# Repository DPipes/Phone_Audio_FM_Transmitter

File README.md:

# Phone Audio FM Transmitter

A device that connects to a smartphone over Bluetooth and transmits the phone's audio over FM. This allows users to listen to their phones over the radio of cars that do not otherwise offer that functionality. In contrast to similar devices on the market, this can scan the FM band and identify an open channel to broadcast on so the user only has to set their car radio to the same station.

This is an electrical engineering senior design project for ECE 445 at the University of Illinois - Urbana Champaign

Team Members:
 - James W.
 - Madigan C.
 - Dan P.

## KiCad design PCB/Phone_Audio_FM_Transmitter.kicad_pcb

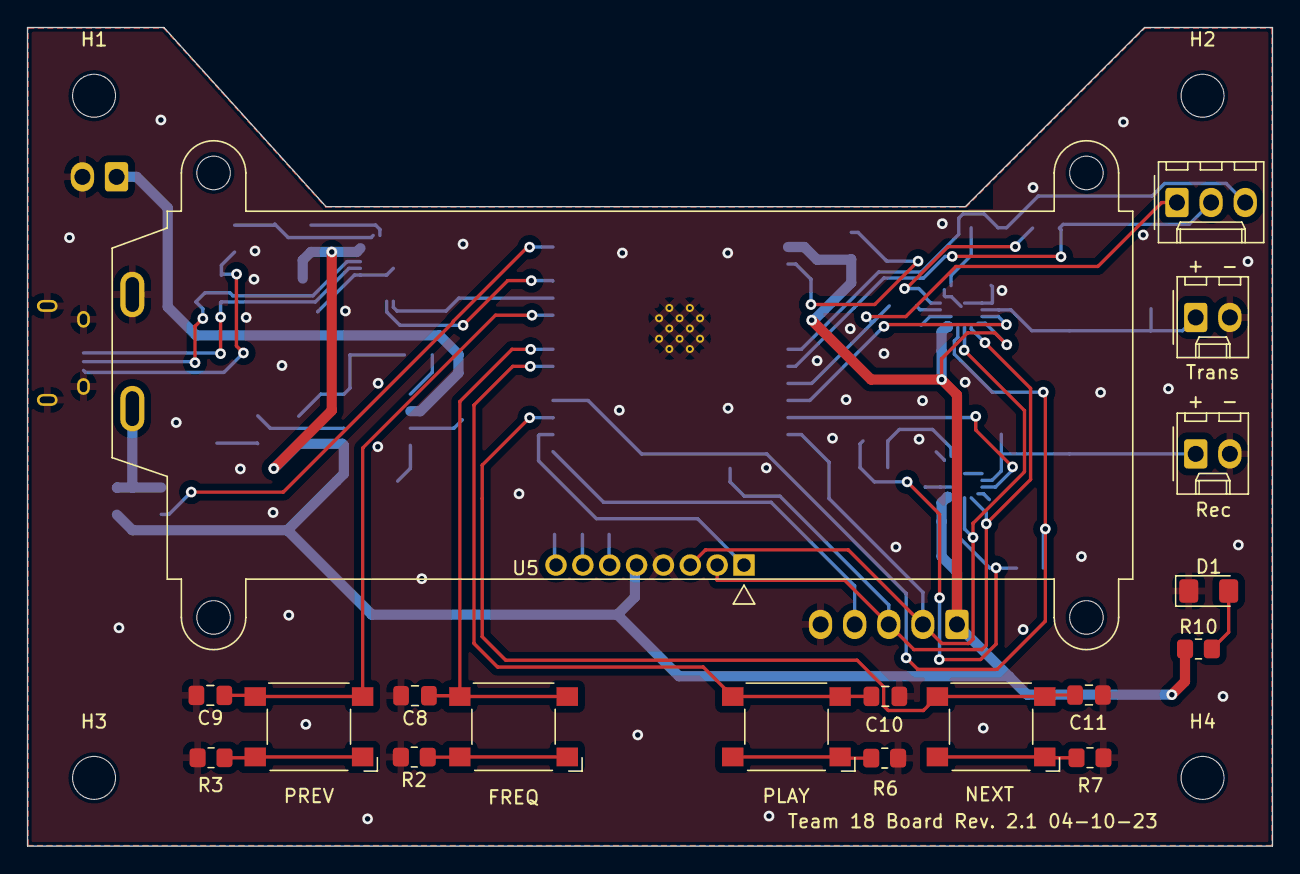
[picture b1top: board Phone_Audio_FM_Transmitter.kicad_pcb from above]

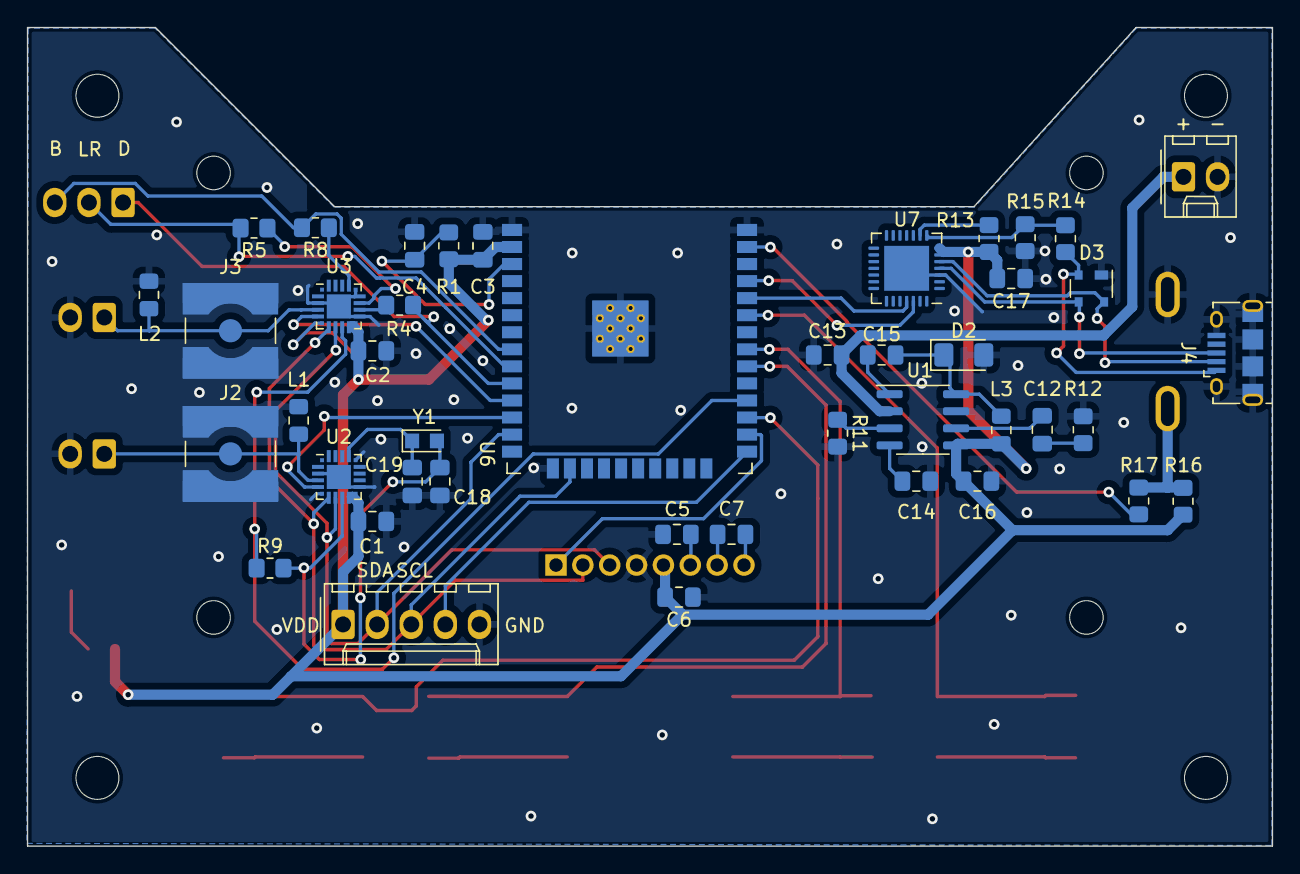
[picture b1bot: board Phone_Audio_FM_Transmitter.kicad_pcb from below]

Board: 2 copper layers, 92.7 x 61.0 mm, 65 parts (43 on the bottom side), 48 nets.

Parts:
C1, C2, C3, C6, C17: 10uF; C_0805_2012Metric_Pad1.18x1.45mm_HandSolder
C4, C5, C7, C8, C9, C10, C11: 1uF; C_0805_2012Metric_Pad1.18x1.45mm_HandSolder
C12: 0.22uF; C_0805_2012Metric_Pad1.18x1.45mm_HandSolder
C13, C16: 22uF; C_0805_2012Metric_Pad1.18x1.45mm_HandSolder
C14: 12nF; C_0805_2012Metric_Pad1.18x1.45mm_HandSolder
C15: 0.1uF; C_0805_2012Metric_Pad1.18x1.45mm_HandSolder
C18, C19: 22pF; C_0805_2012Metric_Pad1.18x1.45mm_HandSolder
D1: LED; LED_1206_3216Metric_Pad1.42x1.75mm_HandSolder
D2: D_Schottky; D_1206_3216Metric_Pad1.42x1.75mm_HandSolder
D3: SP0503BAHT; SOT-143
H1, H2, H3, H4: MountingHole; MountingHole_3.2mm_M3
J1: Vin; Molex_KK-254_AE-6410-02A_1x02_P2.54mm_Vertical
J2, J3: Conn_Coaxial; SMA_Amphenol_132134-10_Vertical
J4: USB_B_Micro; USB_Micro-B_Amphenol_10118194_Horizontal
J5: Test Point; Molex_KK-254_AE-6410-05A_1x05_P2.54mm_Vertical
J6: Rec; Molex_KK-254_AE-6410-02A_1x02_P2.54mm_Vertical
J7: Trans; Molex_KK-254_AE-6410-02A_1x02_P2.54mm_Vertical
J8: I2S Test Point; Molex_KK-254_AE-6410-03A_1x03_P2.54mm_Vertical
L1, L2: 120nH; L_0805_2012Metric_Pad1.15x1.40mm_HandSolder
L3: 13uH; L_0805_2012Metric_Pad1.15x1.40mm_HandSolder
R1, R2, R3, R6, R7, R10: 10k; R_0805_2012Metric_Pad1.20x1.40mm_HandSolder
R4: 600; R_0805_2012Metric_Pad1.20x1.40mm_HandSolder
R5, R8: 2k; R_0805_2012Metric_Pad1.20x1.40mm_HandSolder
R9: 0; R_0805_2012Metric_Pad1.20x1.40mm_HandSolder
R11: 82k; R_0805_2012Metric_Pad1.20x1.40mm_HandSolder
R12: 2.2k; R_0805_2012Metric_Pad1.20x1.40mm_HandSolder
R13: 1k; R_0805_2012Metric_Pad1.20x1.40mm_HandSolder
R14: 22.1k; R_0805_2012Metric_Pad1.20x1.40mm_HandSolder
R15: 47.5k; R_0805_2012Metric_Pad1.20x1.40mm_HandSolder
R16, R17: 100; R_0805_2012Metric_Pad1.20x1.40mm_HandSolder
SW1, SW2, SW3, SW4: SW_Push; SW_SPST_Omron_B3FS-101xP
U1: TPS5403; SOIC-8_3.9x4.9mm_P1.27mm
U2: Si4706; SiliconLabs_QFN-20-1EP_3x3mm_P0.5mm_EP1.8x1.8mm
U3: Si4711; SiliconLabs_QFN-20-1EP_3x3mm_P0.5mm_EP1.8x1.8mm
U5: NHD-C0220BIZ; NHD-C0220BiZ
U6: ESP32-WROOM-32
U7: CP2102N-Axx-xQFN28; QFN-28-1EP_5x5mm_P0.5mm_EP3.35x3.35mm
Y1: 32.768kHz; Crystal_SMD_2012-2Pin_2.0x1.2mm_HandSoldering

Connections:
+3.3V: C1.2, C2.2, C3.2, C6.2, C16.1, C17.2, J5.1, L3.2, R1.2, R10.1, R13.1, R16.1, U1.5 (VSENSE), U2.10 (VD), U2.11 (VA), U3.6 (~SEN), U3.10 (VIO), U3.11 (VDD), U5.5 (VDD), U6.2 (VDD), U7.6 (VDD), U7.7 (VREGIN)
/I2C_SCL: J5.3, U2.7 (SCLK), U3.7 (SCLK), U5.2 (SCL), U6.16 (IO13)
/I2C_SDA: J5.2, U2.8 (SDIO), U3.8 (SDIO), U5.3 (SDA), U6.13 (IO14)
/I2S_BCLK: J8.3, R8.2, U6.8 (IO32)
/I2S_DATA: J8.1, R4.2, U6.10 (IO25)
/I2S_LRCLK: J8.2, R5.2, U6.9 (IO33)
/RGPO3: C19.1, U2.17 (GPO3/DCLK), Y1.1
/RRCLK: C18.1, R9.2, U2.9 (RCLK), Y1.2
/RXDO: U6.34 (RXD0/IO3), U7.25 (RXD)
/RX_RST: U2.5 (~RST), U6.12 (IO27)
/TRCLK: R9.1, U3.9 (RCLK), U6.28 (IO17)
/TXDO: U6.35 (TXD0/IO1), U7.26 (TXD)
/TX_RST: U3.5 (~RST), U6.11 (IO26)
/User Interface/BOOT: J5.4, U6.25 (IO0)
/User Interface/CHANGE_FREQ: C8.1, SW1.2, U6.31 (IO19)
/User Interface/DISP_RST: U5.1 (~RST), U6.26 (IO4)
/User Interface/LCD_BKLT: R17.2, U6.37 (IO23)
/User Interface/NEXT: C11.1, SW4.2, U6.27 (IO16)
/User Interface/PLAY/PAUSE: C10.1, SW3.2, U6.30 (IO18)
/User Interface/PREV: C9.1, SW2.2, U6.33 (IO21)
GND: C1.1, C2.1, C3.1, C4.1, C5.2, C6.1, C8.2, C9.2, C10.2, C11.2, C13.2, C14.2, C16.2, C17.1, C18.2, C19.2, D1.1 (K), D2.2 (A), D3.1 (A), J1.2, J2.2 (Ext), J3.2 (Ext), J4.5 (GND), J4.6 (Shield), J5.5, J6.2, J7.2, L1.1, L2.1, R2.1, R3.1, R6.1, R7.1, R11.2, R12.2, R15.1, U1.7 (GND), U2.3 (RFGND), U2.6 (~SEN), U2.12 (GND), U2.16 (DFS), U2.21 (GND), U3.3 (RFGND), U3.12 (GND), U3.15 (RIN), U3.16 (LIN), U3.21 (GND), U5.4 (VSS), U5.10 (K), U6.1 (GND), U6.15 (GND), U6.38 (GND), U6.39 (GND), U7.3 (GND), U7.29 (GND)
unnamed: C12.2, R12.1
unnamed: D1.2 (A), R10.2
unnamed: C15.2, D2.1 (K), L3.1, U1.8 (LX)
unnamed: C13.1, J1.1, U1.2 (VIN)
unnamed: J2.1 (In), J6.1, L1.2, U2.4 (LPI)
unnamed: J3.1 (In), J7.1, L2.2, U3.4 (TXO)
unnamed: D3.3 (K), J4.3 (D+), U7.4 (D+)
unnamed: D3.4 (K), J4.2 (D-), U7.5 (D-)
unnamed: D3.2 (K), J4.1 (VBUS), R14.1
unnamed: R2.2, SW1.1
unnamed: R3.2, SW2.1
unnamed: R6.2, SW3.1
unnamed: R7.2, SW4.1
unnamed: C15.1, U1.1 (BOOT)
unnamed: C12.1, U1.6 (COMP)
unnamed: R11.1, U1.3 (ROSC)
unnamed: C14.1, U1.4 (SS)
unnamed: R5.1, U3.14 (DFS)
unnamed: R4.1, U3.13 (DIN)
unnamed: R8.1, U3.17 (GPO3/DCLK)
unnamed: R16.2, R17.1, U5.9 (A)
unnamed: C7.1, U5.7 (C1+)
unnamed: C7.2, U5.8 (C1-)
unnamed: C5.1, U5.6 (VOUT)
unnamed: C4.2, R1.1, U6.3 (EN)
unnamed: R14.2, R15.2, U7.8 (VBUS)
unnamed: R13.2, U7.9 (~RST)

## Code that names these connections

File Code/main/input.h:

#include <stdio.h>
#include "driver/gpio.h"
#include "i2c_main.h"

#define CHANGE_FREQ_PIN 19
#define PLAY_PAUSE_PIN  18
#define PREV_PIN        21
#define NEXT_PIN        16

/**
 * @brief Initialize the user input pins
 */
void input_init(void);

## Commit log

2023-03-05 Added datasheets and PCB files
2023-03-05 Added voltage regulator components to finish schematic
2023-03-05 Added first revision of layout. Needs antennae and possibly I2S test points.
2023-03-05 Updated design rules for PCBWay
2023-03-05 Generated Gerber files
2023-03-06 Finished Rev. 1 layout with Gerber files
2023-03-09 Case Revision 1
2023-03-15 added a couple datasheets
2023-03-15 Reorganized some files
2023-03-22 Added basic software framework
2023-03-23 Display init and write functions implemented
2023-03-27 created new fm branch and wrote some comments in rec.c just to make a change
2023-03-27 Changed microcontroller from ESP32-S3 to ESP32 and added UART bridge
2023-03-28 added document explaining how things work + containing my questions, ppartially wrote the powerup function
2023-03-29 Completed PCB Rev 2. Changed microcontroller to ESP32-WROOM-32, added UART bridge, removed button pull-up resistors, added I2S test point, added option to control backlight, and better organized all 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
2023-03-29 Added resistors to I2S pins on transmitter
2023-03-29 Added UART bridge datasheet
2023-03-30 added 'i2c_address_only_read' to read from a device on i2c bus using only an address
2023-03-30 added 'i2c_write_read' to the i2c files to allow a write followed by a read because this is the structure of every signle command for transceiver chips
2023-03-30 added 'trans_command' to transmitter files, used that function to write the power_up function
2023-03-30 changed name of power_up fcn and fixed an issue with it
2023-04-02 fixed power up, changed write and read, changed send command to include delay
2023-04-02 added change frequency function
2023-04-04 transmitter functions mostly done, might want some wrapper functions to set specific properties but it's in working condition now
2023-04-04 wrote a couple receiver functions
2023-04-09 git ignore stuff
2023-04-09 everything we need to run the receiver, aside from some wrapper functions
2023-04-11 Added crystal oscillator for receiver IC and RCLK from ESP32 to FM ICs
2023-04-16 added functions to set reference clock propertiees
2023-04-17 added functions to run the transmitter
2023-04-17 bugs squashed, pins updated
2023-04-18 fully working a2dp audio over i2s, limited avrc functionality
2023-04-18 removed READMEs
2023-04-19 AVRC commands fully implemented
2023-04-19 removed conflicting files
2023-04-19 Added Bluetooth and who knows what else
2023-04-20 Bluetooth audio -> FM completed
2023-04-20 Frequency changing works
2023-04-20 Frequency checking mostly works
2023-04-24 Cleaned code and changed frequency selection stuffs
2023-04-25 Updated channel select
2023-04-25 RDS stuff
2023-04-29 Changed schematic to reflect final design
2023-05-01 final changes
